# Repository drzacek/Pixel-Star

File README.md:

# Pixel-Star
PCB star with RGB LEDs, xmas decoration

!! Warning !!
This is still a work in progress - I am still waiting for my first PCBs to arrive from JLCPCB.
Once I have them done I will update this repo with pictures and firmware source code.

With this project you can make a simple yet nice star-shaped PCB with a bunch of addressable LEDs.

It has STM32 microcontroller on board and this project provides software for it to drive the LEDs.

In order to make it:

1. Download KiCAD 6, STM32CubeIDE, clone/download this project
2. Generate Gerber files according to your manufarcturer rules (for example [JLCPCB](https://support.jlcpcb.com/article/194-how-to-generate-gerber-and-drill-files-in-kicad-6))
3. Order the PCB
4. Order the parts (Kicad project contains links to all parts on lcsc)
5. Solder everything
6. Compile the STM32 project
7. Flash the firmware using ST-Link

### Bill of Materials

|  Pos. | Name  | Link  | Amount  |
| ------------ | ------------ | ------------ | ------------ |
| 1.  | Capacitor 10µF 1206  | [Link](https://www.lcsc.com/product-detail/Multilayer-Ceramic-Capacitors-MLCC-SMD-SMT_Samsung-Electro-Mechanics-CL31B106KAHNNNE_C14860.html)  |  2  |
| 2.  | Capacitor 100nf 0805  | [Link](https://www.lcsc.com/product-detail/Multilayer-Ceramic-Capacitors-MLCC-SMD-SMT_CCTC-TCC0805X7R104K500DT_C282732.html)  | 17  |
| 3.  | Capacitor 4.7µF 1206  | [Link](https://www.lcsc.com/product-detail/Multilayer-Ceramic-Capacitors-MLCC-SMD-SMT_Samwha-Capacitor-CS3216X7R475K160NRI_C5189824.html)  | 1  |
| 4.  | WS2813E RGB LED  | [Link](https://www.lcsc.com/product-detail/Light-Emitting-Diodes-LED_Worldsemi-WS2813E_C160214.html)  | 11  |
| 5.  | LED 1206 Emerald  | [Link](https://www.lcsc.com/product-detail/Light-Emitting-Diodes-LED_XINGLIGHT-XL-3216UGC_C965825.html)  | 5  |
| 6.  | USB-C Connector  | [Link](https://www.lcsc.com/product-detail/USB-Connectors_SHOU-HAN-TYPE-C-16PIN-2MD-073_C2765186.html)  | 1  |
| 7.  | Picoblade 1x4 Connector  | [Link](https://www.lcsc.com/product-detail/Wire-To-Board-Wire-To-Wire-Connector_MOLEX-532610471_C240847.html)  | 1  |
| 8.  | Resistor 5.11k 0805  | [Link](https://www.lcsc.com/product-detail/Chip-Resistor-Surface-Mount_UNI-ROYAL-Uniroyal-Elec-0805W8F5111T5E_C46039.html)  | 2  |
| 9.  | Resistor 1k 0805  | [Link](https://www.lcsc.com/product-detail/Chip-Resistor-Surface-Mount_FOJAN-FRC0805F1001TS_C2907232.html)  | 2  |
| 10.  | Resistor 10k 0805  | [Link](https://www.lcsc.com/product-detail/Chip-Resistor-Surface-Mount_UNI-ROYAL-Uniroyal-Elec-0805W8F1002T5E_C17414.html)  | 2  |
| 11.  | Resistor 47 Ohm 0805  | [Link](https://www.lcsc.com/product-detail/Chip-Resistor-Surface-Mount_Walsin-Tech-Corp-WR08X47R0FTL_C168456.html)  | 5  |
| 12.  | Button  | [Link](https://www.lcsc.com/product-detail/Tactile-Switches_Korean-Hroparts-Elec-K2-1107ST-A4DW-06_C118141.html)  | 3  |
| 13.  | Voltage regulator 3.3V  | [Link](https://www.lcsc.com/product-detail/Linear-Voltage-Regulators-LDO_HEERMICR-AMS1117-3-3_C5199435.html)  | 1  |
| 14.  | MCU STM32G030  | [Link](https://www.lcsc.com/product-detail/Microcontroller-Units-MCUs-MPUs-SOCs_STMicroelectronics-STM32G030F6P6TR_C529330.html)  | 1  |
| 15.  | Level shifter  | [Link](https://www.lcsc.com/product-detail/Buffers-Drivers_Texas-Instruments-SN74LV1T34DBVR_C100024.html)  | 1  |

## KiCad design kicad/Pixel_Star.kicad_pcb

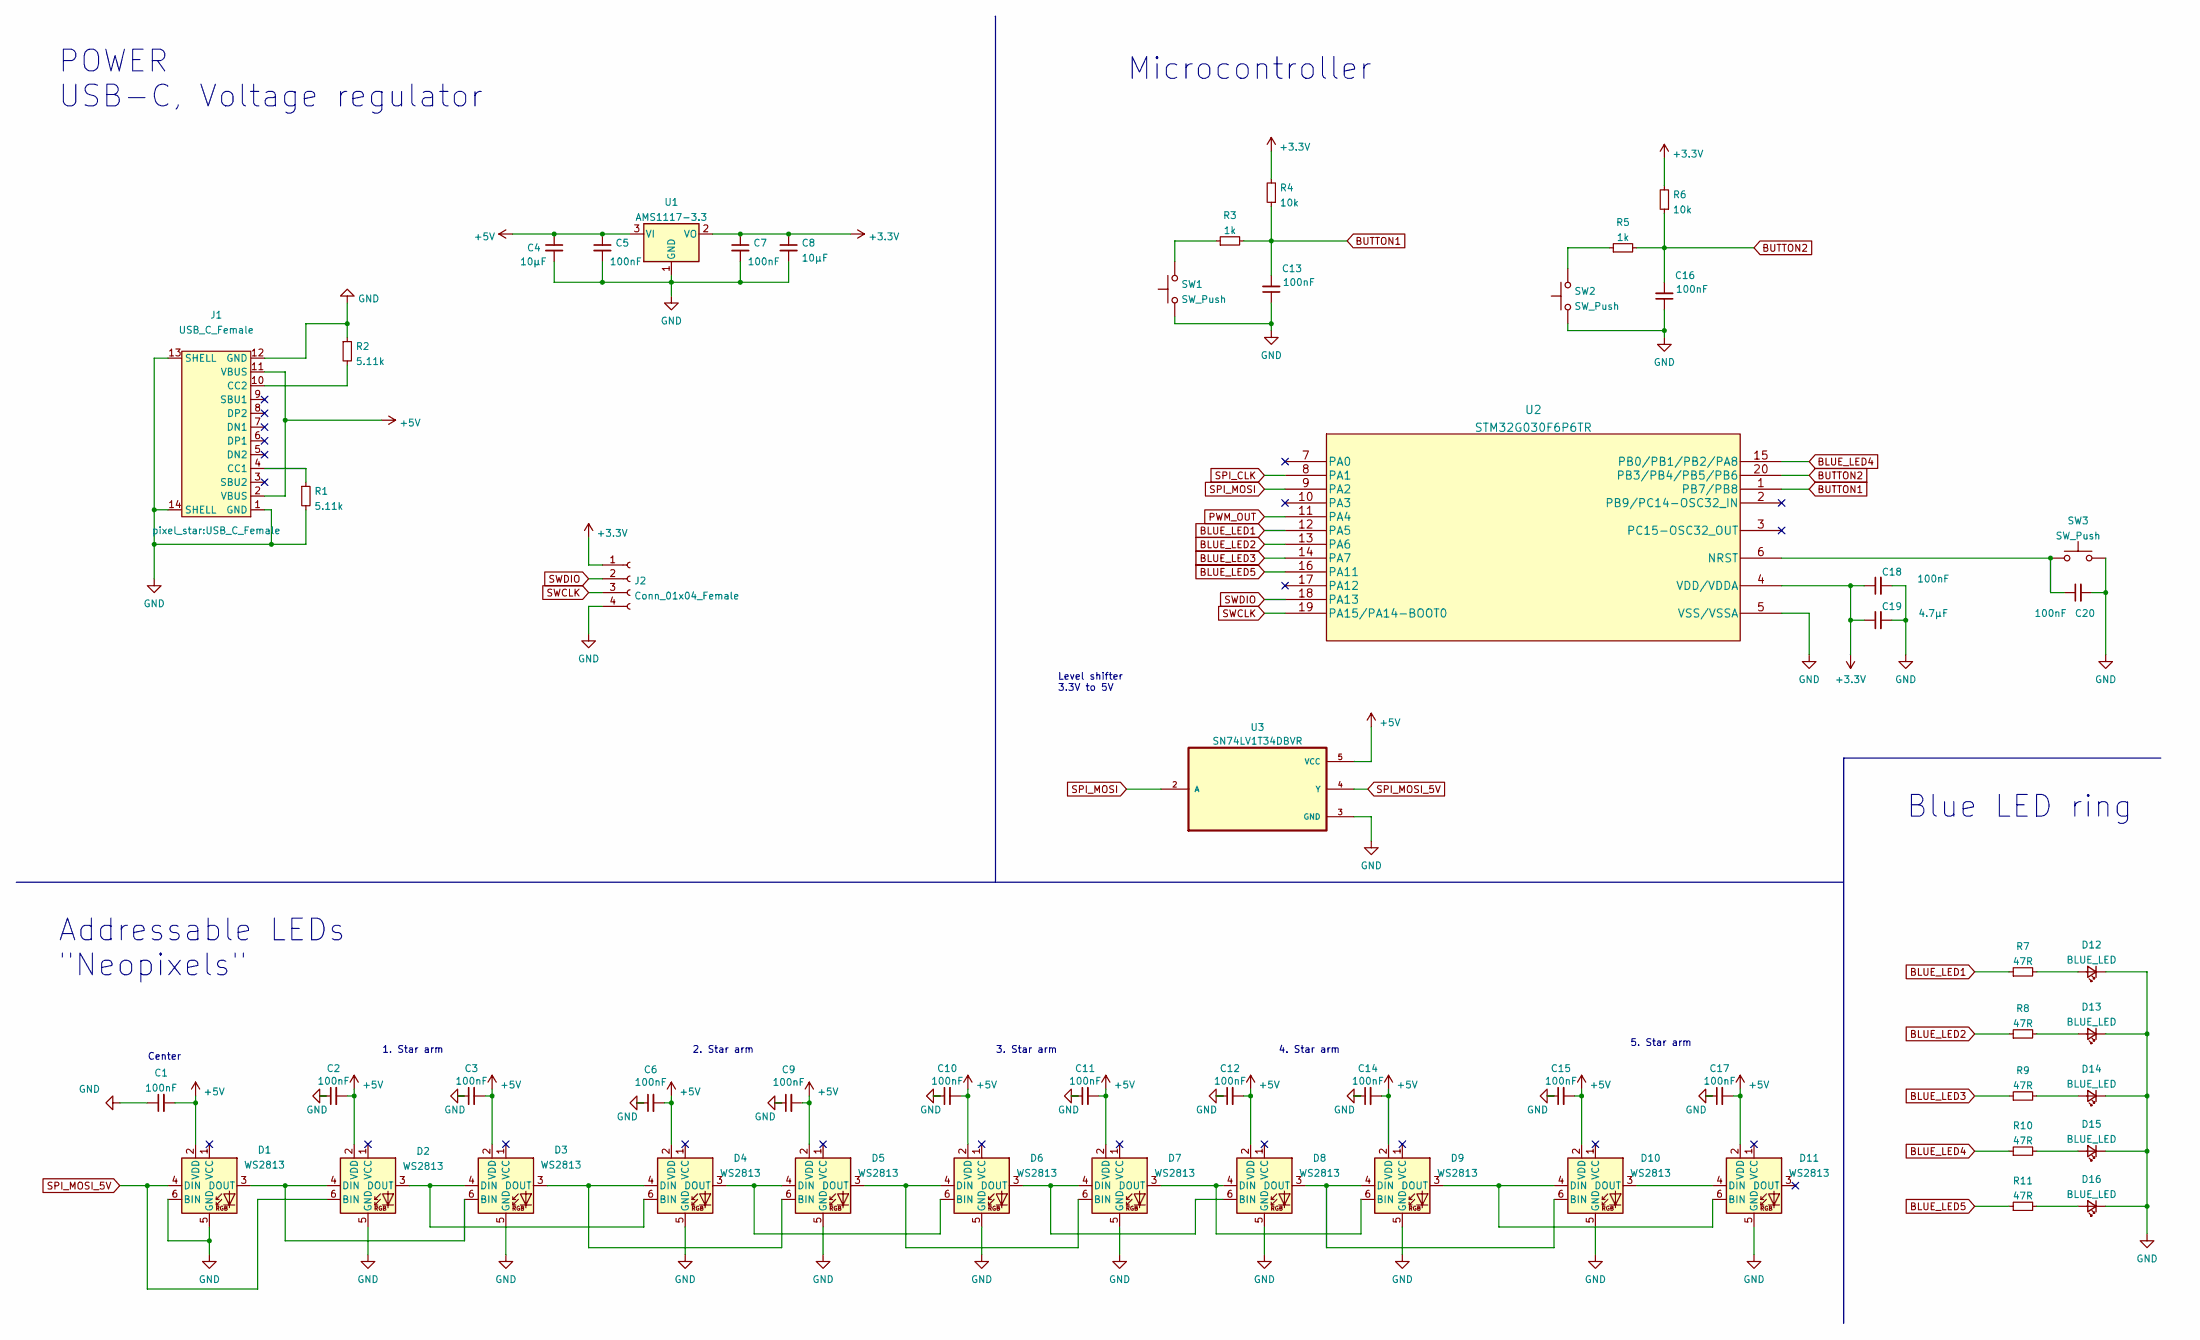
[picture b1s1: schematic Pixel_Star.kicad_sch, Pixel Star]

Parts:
C1, C2, C3, C5, C6, C7, C9, C10, C11, C12, C13, C14, C15, C16, C17, C18, C20: 100nF; C_0805_2012Metric_Pad1.18x1.45mm_HandSolder
C4, C8: 10µF; C_1206_3216Metric_Pad1.33x1.80mm_HandSolder
C19: 4.7µF; C_1206_3216Metric_Pad1.33x1.80mm_HandSolder
D1, D2, D3, D4, D5, D6, D7, D8, D9, D10, D11: WS2813; LED_WS2812_PLCC6_5.0x5.0mm_P1.6mm
D12, D13, D14, D15, D16: BLUE_LED; LED_1206_3216Metric_Pad1.42x1.75mm_HandSolder
J1: USB_C_Female
J2: Conn_01x04_Female; Molex_PicoBlade_53261-0471_1x04-1MP_P1.25mm_Horizontal
R1, R2: 5.11k; R_0805_2012Metric_Pad1.20x1.40mm_HandSolder
R3, R5: 1k; R_0805_2012Metric_Pad1.20x1.40mm_HandSolder
R4, R6: 10k; R_0805_2012Metric_Pad1.20x1.40mm_HandSolder
R7, R8, R9, R10, R11: 47R; LED_0805_2012Metric_Pad1.15x1.40mm_HandSolder
SW1, SW2, SW3: SW_Push; K2-1107ST-A4DW-06
U1: AMS1117-3.3; SOT-223-3_TabPin2
U2: STM32G030F6P6TR
U3: SN74LV1T34DBVR; SOT95P280X145-5N

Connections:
+3V3: C7.1, C8.1, C18.1, C19.1, J2.1, R4.2, R6.2, U1.2 (VO), U2.4 (VDD/VDDA)
+5V: C1.2, C2.2, C3.2, C4.1, C5.1, C6.2, C9.2, C10.2, C11.2, C12.2, C14.2, C15.2, C17.2, D1.2 (VDD), D2.2 (VDD), D3.2 (VDD), D4.2 (VDD), D5.2 (VDD), D6.2 (VDD), D7.2 (VDD), D8.2 (VDD), D9.2 (VDD), D10.2 (VDD), D11.2 (VDD), J1.2 (VBUS), J1.11 (VBUS), U1.3 (VI), U3.5 (VCC)
BLUE_LED1: R7.1, U2.12 (PA5)
BLUE_LED2: R8.1, U2.13 (PA6)
BLUE_LED3: R9.1, U2.14 (PA7)
BLUE_LED4: R10.1, U2.15 (PB0/PB1/PB2/PA8)
BLUE_LED5: R11.1, U2.16 (PA11)
BUTTON1: C13.2, R3.2, R4.1, U2.1 (PB7/PB8)
BUTTON2: C16.2, R5.2, R6.1, U2.20 (PB3/PB4/PB5/PB6)
GND: C1.1, C2.1, C3.1, C4.2, C5.2, C6.1, C7.2, C8.2, C9.1, C10.1, C11.1, C12.1, C13.1, C14.1, C15.1, C16.1, C17.1, C18.2, C19.2, C20.2, D1.5 (GND), D1.6 (BIN), D2.5 (GND), D3.5 (GND), D4.5 (GND), D5.5 (GND), D6.5 (GND), D7.5 (GND), D8.5 (GND), D9.5 (GND), D10.5 (GND), D11.5 (GND), D12.1 (K), D13.1 (K), D14.1 (K), D15.1 (K), D16.1 (K), J1.1 (GND), J1.12 (GND), J1.13 (SHELL), J1.14 (SHELL), J2.4, R1.2, R2.1, SW1.1, SW2.1, SW3.2, U1.1 (GND), U2.5 (VSS/VSSA), U3.3 (GND)
unnamed: C20.1, SW3.1, U2.6 (NRST)
unnamed: D1.3 (DOUT), D2.4 (DIN), D3.6 (BIN)
unnamed: D2.3 (DOUT), D3.4 (DIN), D4.6 (BIN)
unnamed: D3.3 (DOUT), D4.4 (DIN), D5.6 (BIN)
unnamed: D4.3 (DOUT), D5.4 (DIN), D6.6 (BIN)
unnamed: D5.3 (DOUT), D6.4 (DIN), D7.6 (BIN)
unnamed: D6.3 (DOUT), D7.4 (DIN), D8.6 (BIN)
unnamed: D7.3 (DOUT), D8.4 (DIN), D9.6 (BIN)
unnamed: D10.3 (DOUT), D11.4 (DIN)
unnamed: D9.3 (DOUT), D10.4 (DIN), D11.6 (BIN)
unnamed: D8.3 (DOUT), D9.4 (DIN), D10.6 (BIN)
unnamed: D12.2 (A), R7.2
unnamed: D13.2 (A), R8.2
unnamed: D14.2 (A), R9.2
unnamed: D15.2 (A), R10.2
unnamed: D16.2 (A), R11.2
unnamed: J1.4 (CC1), R1.1
unnamed: J1.10 (CC2), R2.2
unnamed: R3.1, SW1.2
unnamed: R5.1, SW2.2
PWM_OUT: U2.11 (PA4)
SPI_CLK: U2.8 (PA1)
SPI_MOSI: U2.9 (PA2), U3.2 (A)
SPI_MOSI_5V: D1.4 (DIN), D2.6 (BIN), U3.4 (Y)
SWCLK: J2.3, U2.19 (PA15/PA14-BOOT0)
SWDIO: J2.2, U2.18 (PA13)

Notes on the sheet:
Level shifter 3.3V to 5V
Addressable LEDs "Neopixels"
Microcontroller
3. Star arm
Center
Blue LED ring
POWER USB-C, Voltage regulator
4. Star arm
1. Star arm
5. Star arm
2. Star arm

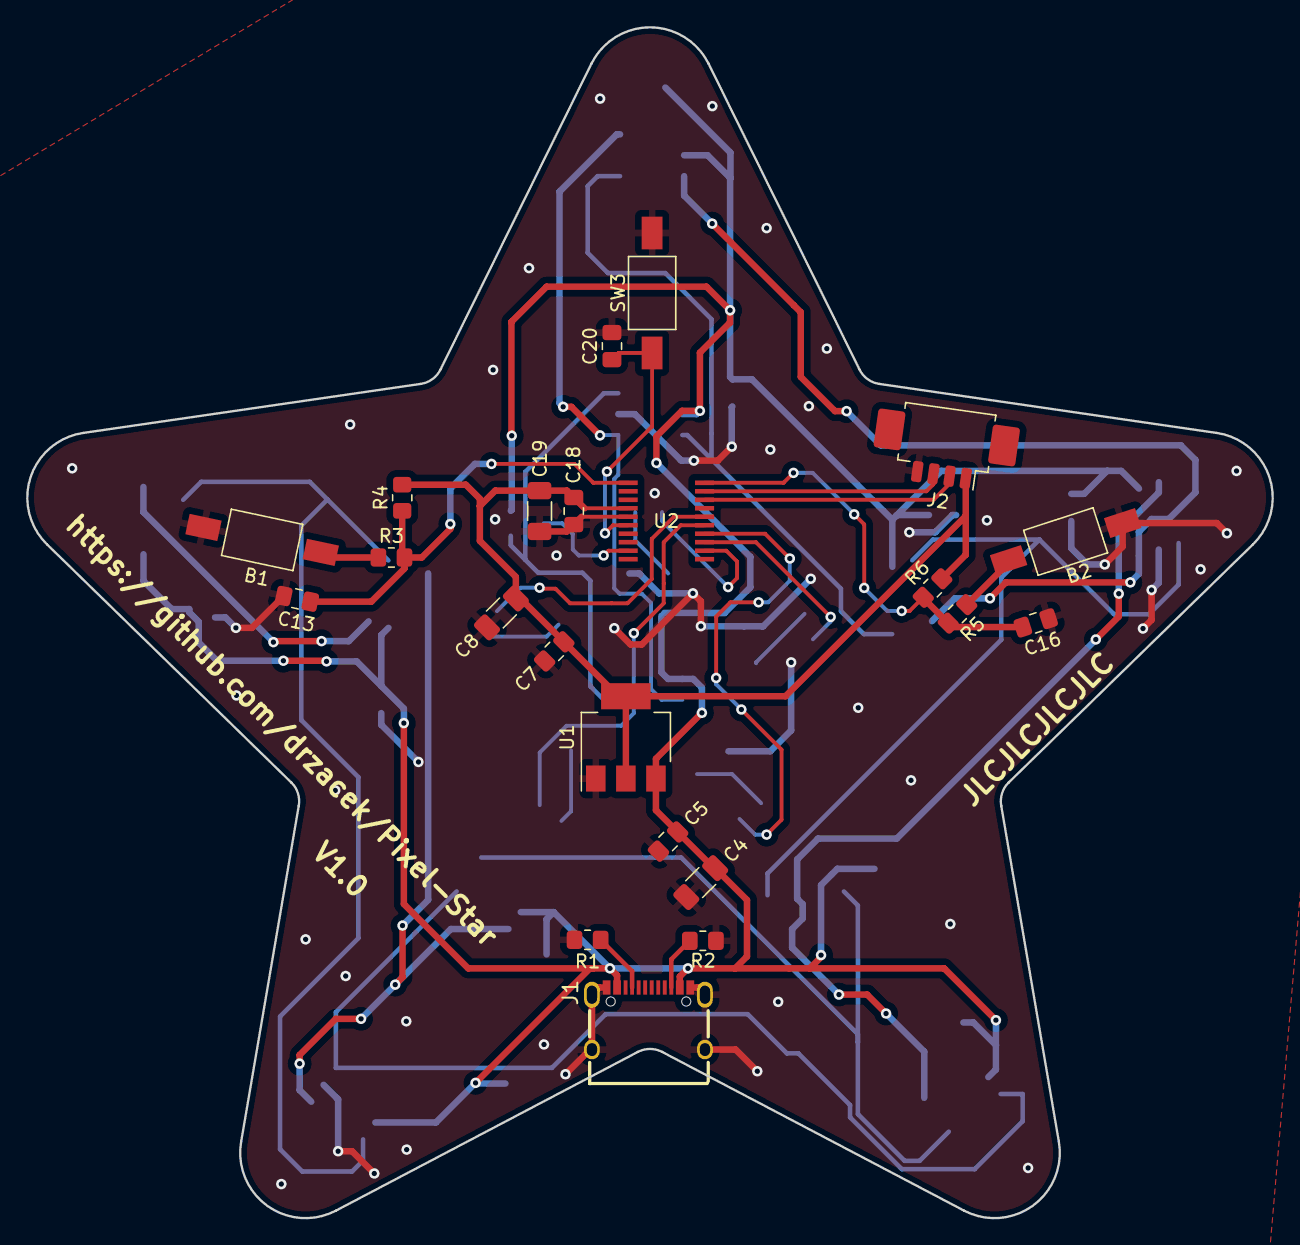
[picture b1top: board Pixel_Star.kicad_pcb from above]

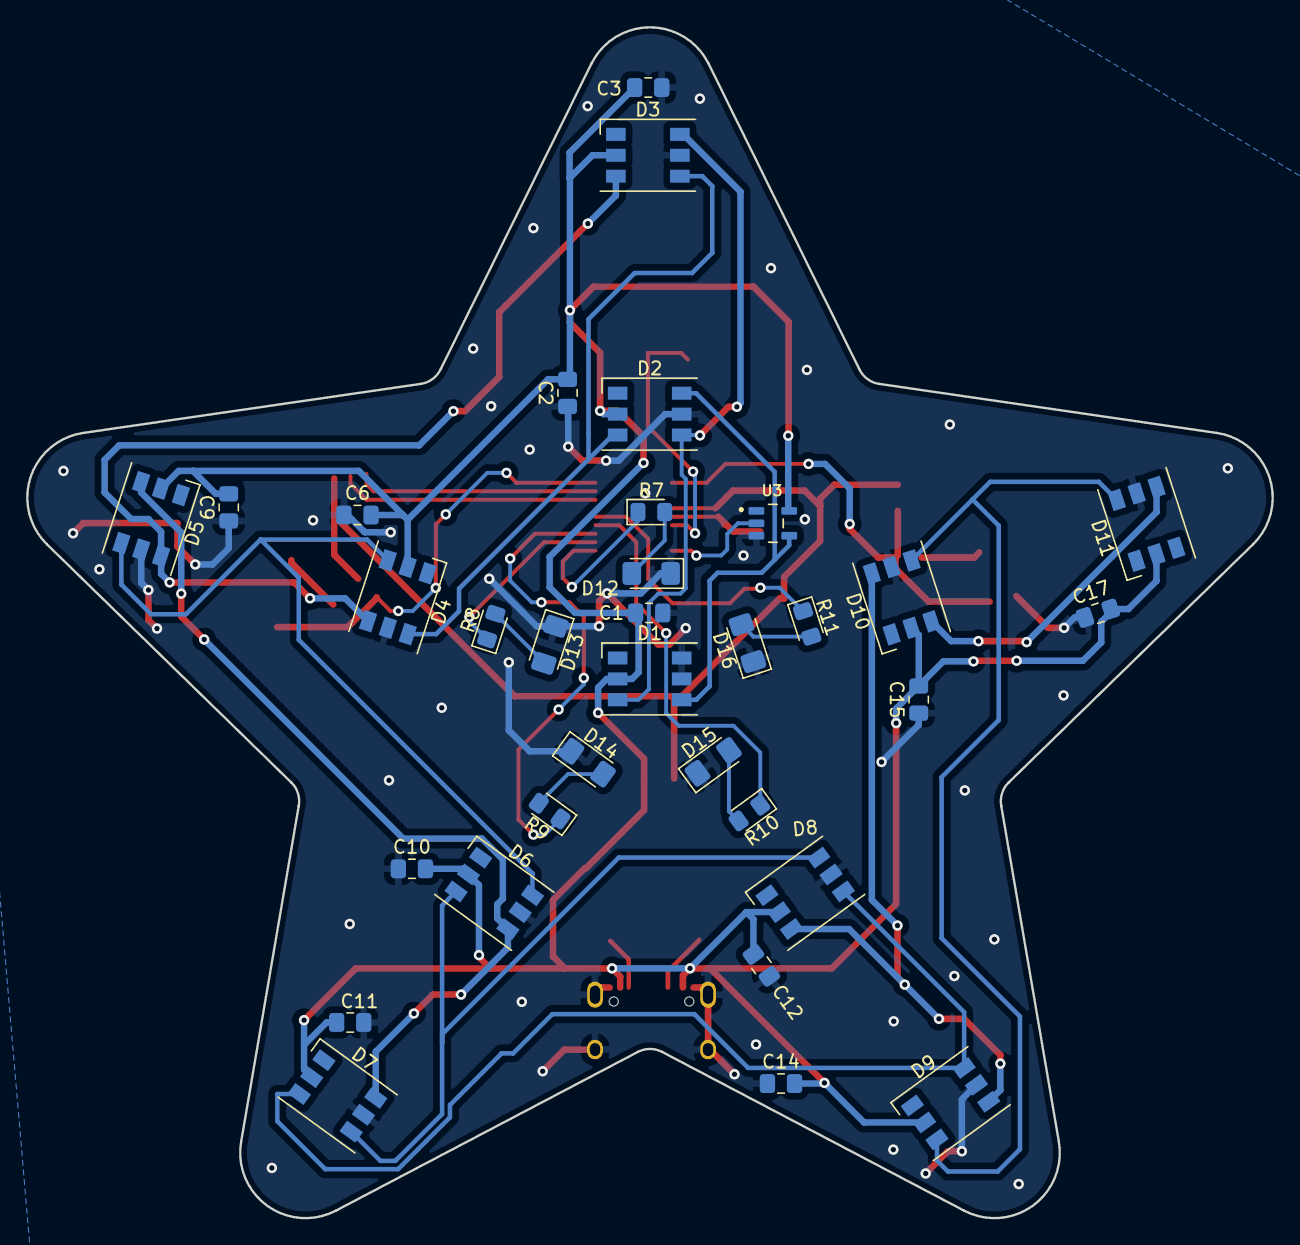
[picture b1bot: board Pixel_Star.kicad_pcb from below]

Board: 2 copper layers, 95.3 x 91.1 mm, 55 parts (33 on the bottom side), 34 nets.

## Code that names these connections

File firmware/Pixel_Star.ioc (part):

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Mcu.Name=STM32G030F6Px
Mcu.Package=TSSOP20
Mcu.UserName=STM32G030F6Px
PA1.Mode=TX_Only_Simplex_Unidirect_Master
PA1.Signal=SPI1_SCK
PA11\ [PA9].GPIOParameters=GPIO_Label
PA11\ [PA9].GPIO_Label=BLU_LED5
PA11\ [PA9].Signal=GPIO_Output
PA13.Mode=Serial_Wire
PA13.Signal=SYS_SWDIO
PA14-BOOT0.Mode=Serial_Wire
PA14-BOOT0.Signal=SYS_SWCLK
PA14-BOOT0__PA15.StandardMode=true
PA2.Mode=TX_Only_Simplex_Unidirect_Master
PA2.Signal=SPI1_MOSI
PA4.Signal=S_TIM14_CH1
PA5.GPIOParameters=GPIO_Label
PA5.GPIO_Label=BLU_LED1
PA5.Signal=GPIO_Output
PA6.GPIOParameters=GPIO_Label
PA6.GPIO_Label=BLU_LED2
PA6.Signal=GPIO_Output
PA7.GPIOParameters=GPIO_Label
PA7.GPIO_Label=BLU_LED3
PA7.Signal=GPIO_Output
PA8.GPIOParameters=GPIO_Label
PA8.GPIO_Label=BLU_LED4
PA8.Signal=GPIO_Output
PB0__PB1__PB2__PA8.StandardMode=true
PB3__PB4__PB5__PB6.StandardMode=true
PB6.GPIOParameters=GPIO_Label
PB6.GPIO_Label=BUTTON2
PB6.Signal=GPIO_Input
PB7__PB8.StandardMode=true
PB8.GPIOParameters=GPIO_Label
PB8.GPIO_Label=BUTTON1
PB8.Signal=GPIO_Input
PC14-OSC32_IN\ (PC14)__PB9.StandardMode=true
RCC.HSE_VALUE=8000000
RCC.SYSCLKFreq_VALUE=64000000
RCC.SYSCLKSource=RCC_SYSCLKSOURCE_PLLCLK
board=custom

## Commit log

2022-10-24 Initial Commit - V1.0
2022-10-24 Fix typo
2022-10-24 Update README.md
    Add WIP disclaimer
2022-10-26 Add render image
2022-10-26 Update README.md
    Add correct url to image
2022-11-05 Improve PCB labels - SWD connector, Reset button
2022-11-07 Add STM32CubeIDE Project, fix kicad project Added base project for the STM32 MCU - so far not much happening, but will act as base for future coding Last commit seems to have broken the kicad project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
2022-11-10 Initial commit with working firmware Only simple animation present, but a base for driving the LEDs is present
2022-11-18 Many fixes, add User Buttons, new animationst Added .gitignore and removed local setting file (.kicad_prl) from git tracking Fixed bit-order in ws2813 protocol - now the colors are properly driven Ad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

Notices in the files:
parts and their libraries:
Copyright 2021 Accelerated Designs. All rights reserved.
